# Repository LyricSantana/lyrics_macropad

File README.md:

# Lyric's Macropad! :D
My custom Macropad made for Hack Club's Blueprint program! I used this project to learn how to create PCBs using KiCad and write KMK files in Python. I plan to use my Macropad for various miscellaneous tasks!

## Showcase Video:
https://youtu.be/G0M81F9X2f0?si=TFrZOab-gzS2jKHI

## Features:
- 5 Reprogrammable Keys
- EC11 Rotary Encoder
- 0.91" 128x32 OLED Display that can be used to display and static BMP image!

## Completed Macropad

## Video Demo
https://youtu.be/G0M81F9X2f0

## CAD
I used Autodesk Fusion 360 to create my case since that's what I already knew how to use!
There are two main pieces to the case: the base, which holds the PCB, and the lid, which covers most of the PCB but leaves the needed parts uncovered.
<table>
  <tr>
    <td>Fully Assembled Macropad<br></td>
  </tr>
</table>
<table>
  <tr>
    <td>Base<br></td>
    <td>Lid <br></td>
  </tr>
</table>

## PCB
My PCB was designed using KiCad, which was my first time using the software. 
<table>
  <tr>
    <td>Schematic<br></td>
    <td>PCB<br></td>
</td>
  </tr>
</table>

## Firmware
My Macropad used KMK firmware for everything. This was my first time using this, and I wasn't able to test it while writing it, so I used a few snippets of code online for a bit of help, but most was written by me. I plan to change what each key does once I'm able to do more testing.
Here's what each key does:
- Key 1: Alt + Tab
- Key 2: Ctrl + Tab
- Key 3: Mouse Middle Click
- Key 4: Alt + F4
- Key 5: Super + L
- Rotary Encoder Rotate: Volume Up/Down
- Rotary Encoder Click: Toggle Mute

## BOM
- 5x Cherry MX Switches
- 1x XIAO RP2040
- 5x Blank DSA Keycaps
- 4x M3x16 Bolt
- 4x M3 Heatset
- 1x 0.91-inch 128x32 OLED display
- 1x EC11 Rotary Encoder
- 1x Lid (macropad_lid.stl)
- 1x Base (macropad_base.stl)

## Information About my Project
### Building
So I have had a soldering iron, but haven't used it in a while, lol, so I had to watch a couple of tutorials to give myself a refresher. After some practice on some scrap PCB boards, I soldered the Seeed XIAO RP2040, 5 switches, rotary encoder, and OLED screen to the PCB. After checking connections with a multimeter, everything seemed to be wired correctly. Afterwards, I 3D printed my case and knob, and it was done! I had so much fun designing, building, and programming this and learn a lot from it!

### Inspiration
I've always wanted a Macropad that I could program each individual component to do whatever I wanted to do. I use keybinds a LOT in most programs I use, so I hope to figure out which ones I use most and modify the code to do what I need. I added the OLED screen last minute because I wanted to add whatever image I wanted onto there! Overall, creating this was super fun, and I learned more than I was expecting!

### Challenges
I had previous experience with Autodesk Fusion 360, but I had never touched KiCad prior to starting this project. The learning curve was pretty steep for me, but once I got the hang of it, it was a lot better! I'm sure that there are lots of things I could have done better in my PCB design, so I would want to continue to do more research and learn best practices. Overall, it was still very fun, despite having to watch multiple tutorials for KiCad, and I learned a lot about the program!

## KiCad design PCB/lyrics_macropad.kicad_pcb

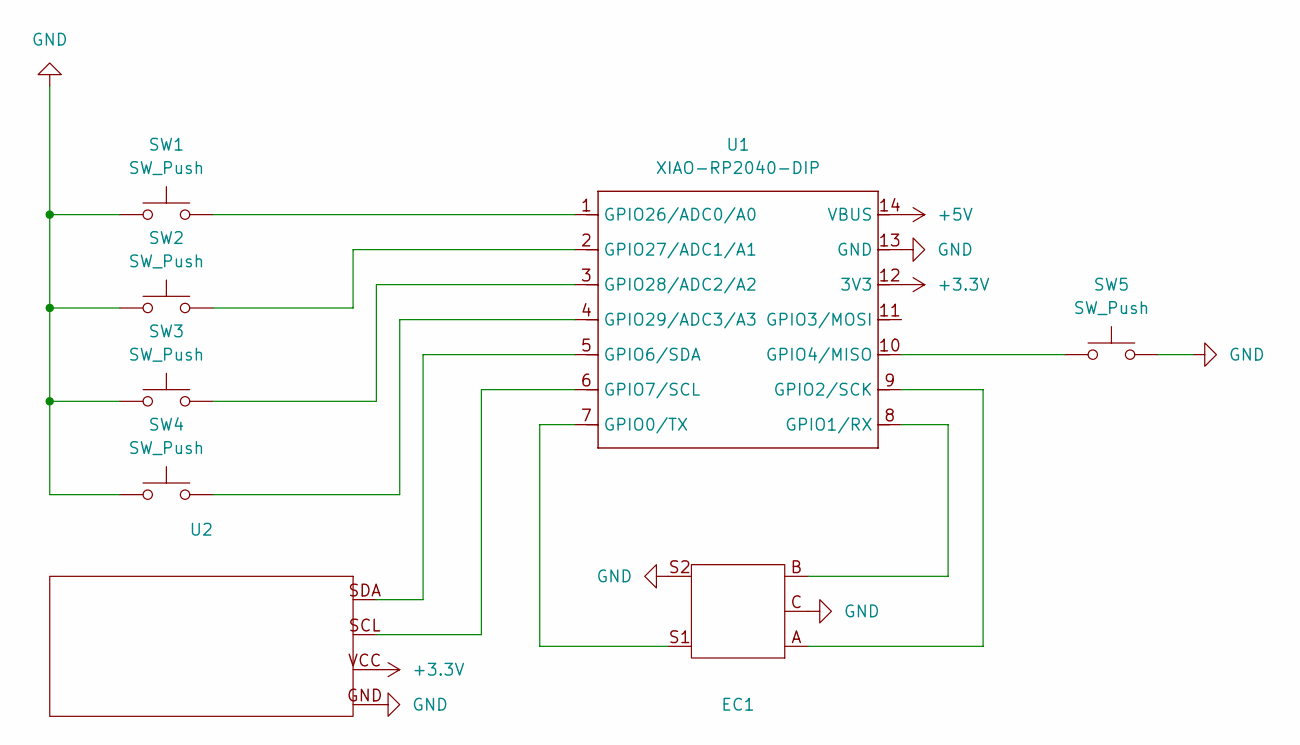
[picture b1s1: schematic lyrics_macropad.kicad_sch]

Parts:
EC1: RotaryEncoder_Alps_EC11E-Switch_Vertical_H20mm
SW1, SW2, SW3, SW4, SW5: SW_Push; SW_Cherry_MX_1.00u_PCB
U1: XIAO-RP2040-DIP
U2: OLED_DISPLAY

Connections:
+3.3V: U1.12 (3V3), U2.VCC
+5V: U1.14 (VBUS)
GND: EC1.C, EC1.S2, SW1.1, SW2.1, SW3.1, SW4.1, SW5.1, U1.13 (GND), U2.GND
unnamed: EC1.S1, U1.7 (GPIO0/TX)
unnamed: EC1.B, U1.8 (GPIO1/RX)
unnamed: EC1.A, U1.9 (GPIO2/SCK)
unnamed: SW5.2, U1.10 (GPIO4/MISO)
unnamed: U1.5 (GPIO6/SDA), U2.SDA
unnamed: U1.6 (GPIO7/SCL), U2.SCL
unnamed: SW1.2, U1.1 (GPIO26/ADC0/A0)
unnamed: SW2.2, U1.2 (GPIO27/ADC1/A1)
unnamed: SW3.2, U1.3 (GPIO28/ADC2/A2)
unnamed: SW4.2, U1.4 (GPIO29/ADC3/A3)

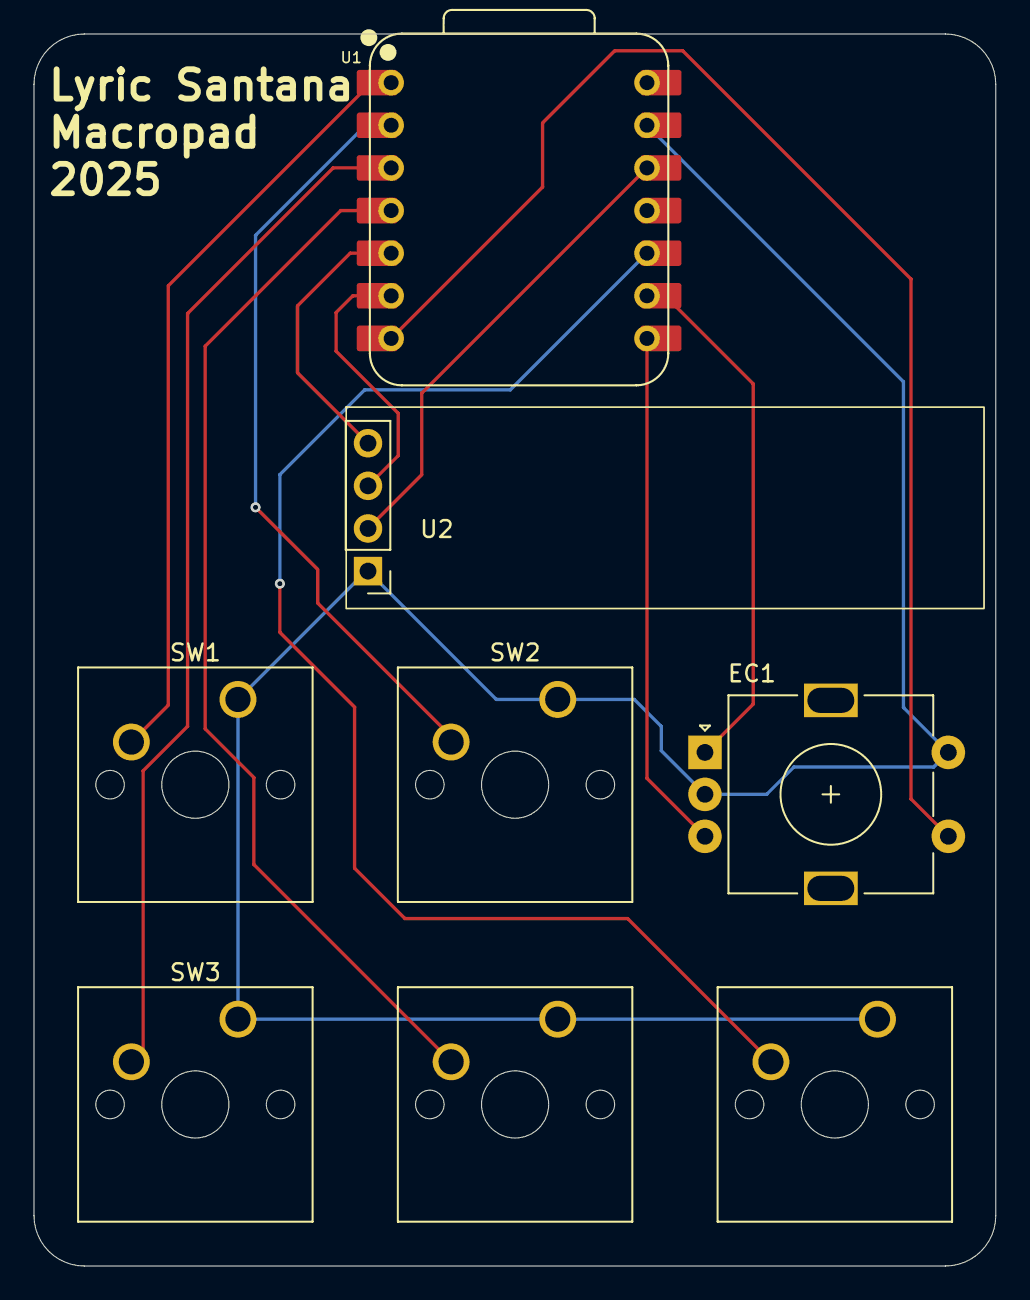
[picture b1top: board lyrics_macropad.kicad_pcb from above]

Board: 2 copper layers, 57.3 x 73.4 mm, 8 parts (0 on the bottom side), 12 nets.

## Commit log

2025-12-07 Expand README with project details and features
2025-12-07 Fix typos and formatting in README.md
    Corrected minor typos and formatting issues in the README.
2025-12-07 Update software names in README
2025-12-07 Add CAD files and update PCB
2025-12-07 Updated CAD Files
2025-12-31 Update README
    Added a video demo link to the README.
